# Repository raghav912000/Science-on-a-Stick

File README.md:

# Science-on-a-Stick
The thought of this project came when I was working in my physics lab. I made this project to overcome the limitations of performing experiments using conventional apparatus. Through this project, we can verify the value of acceleration due to gravity, Faraday's  Law and Lenz's Law with more accuracy and fewer efforts.  I use Arduino to convert analog value ( voltage across a coil) into digital values and send it to the laptop. I write a python code which receives data send by Arduino and plot the corresponding analog value. Through this curve, we can easily observe the maximum voltage across a coil. We can also verify Lenz's Law by the sinusoidal nature of the curve. I also use hall switch to give an interrupt to Arduino when a magnet passes it. By these interrupts, I can measure the time between any two points with more accuracy.
# trial

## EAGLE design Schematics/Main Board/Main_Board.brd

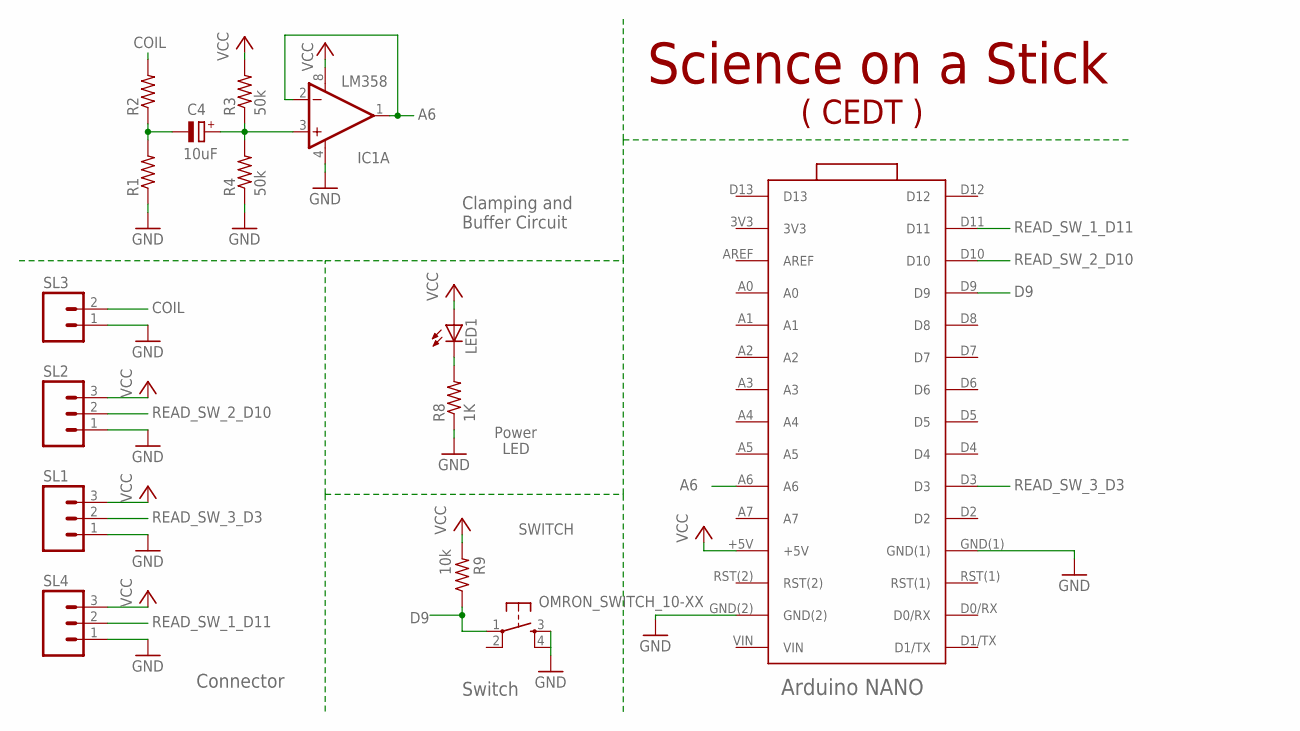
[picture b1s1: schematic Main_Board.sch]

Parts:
C4: 10uF; E2,5-5
IC1: LM358; DIP08
LED1: LED3MM
R1, R2: RESISTOR0207/7; 0207/7
R3, R4: 50k; 0207/7
R8: 1K; 0207/7
R9: 10k; 0207/7
SL1, SL2, SL4: M03; 03P
SL3: M02; 02P
SWITCH: OMRON_SWITCH_10-XX; B3F-10XX
U$1: ARDUINO_NANO_3_ARDUINO(NANO_3.0); ARDUINO_NANO_3_ARDUINO_NANO_30PIN

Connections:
A6: IC1.1 (OUT), IC1.2 (-IN), U$1.A6
CLAMP_SIGNAL: C4.+, IC1.3 (+IN), R3.1, R4.2
COIL: R2.2, SL3.2
D9: R9.1, SWITCH.1, U$1.D9
GND: IC1.4 (V-), R1.1, R4.1, R8.1, SL1.1, SL2.1, SL3.1, SL4.1, SWITCH.3 (S), SWITCH.4 (S1), U$1.GND(1), U$1.GND(2)
unnamed: C4.-, R1.2, R2.1
unnamed: LED1.K (C), R8.2
READ_SW_1_D11: SL4.2, U$1.D11
READ_SW_2_D10: SL2.2, U$1.D10
READ_SW_3_D3: SL1.2, U$1.D3
VCC: IC1.8 (V+), LED1.A, R3.2, R9.2, SL1.3, SL2.3, SL4.3, U$1.+5V

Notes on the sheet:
Arduino NANO
Science on a Stick
( CEDT )
Power
LED
Switch
Connector
Clamping and Buffer Circuit

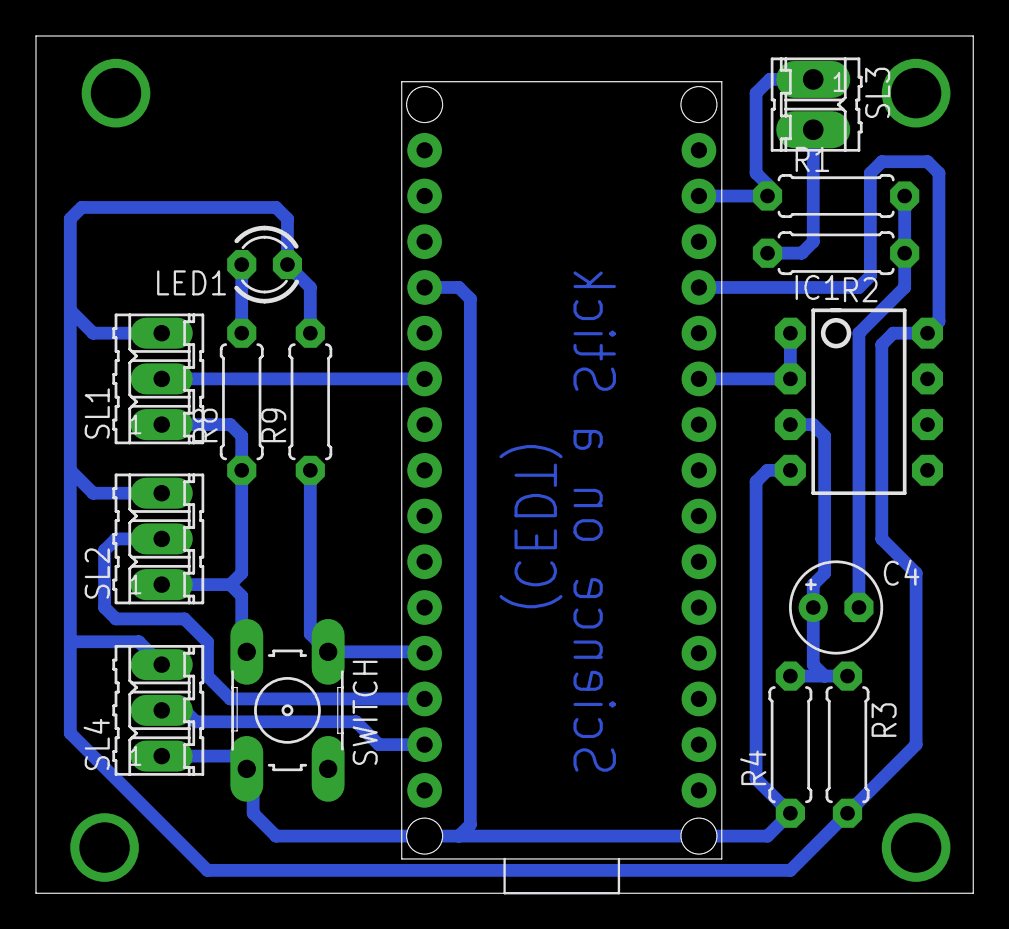
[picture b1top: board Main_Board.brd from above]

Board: 2 copper layers, 52.1 x 47.6 mm, 15 parts (0 on the bottom side), 11 nets.

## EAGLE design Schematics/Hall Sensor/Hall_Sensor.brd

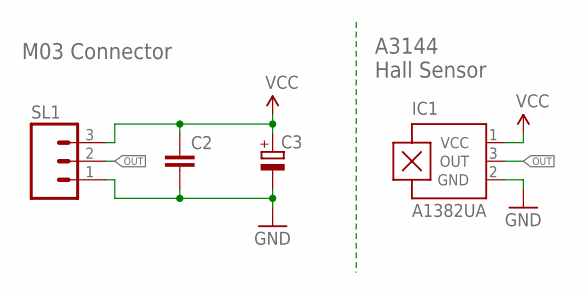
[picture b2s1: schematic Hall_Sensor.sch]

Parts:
C2: C-EU025-025X050; C025-025X050
C3: CPOL-EUE2,5-6E; E2,5-6E
IC1: A1382UA; SIP3-UA
SL1: M03; 03P

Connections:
GND: C2.2, C3.-, IC1.2 (GND), SL1.1
OUT: IC1.3 (OUT), SL1.2
VCC: C2.1, C3.+, IC1.1 (VCC), SL1.3

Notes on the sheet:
M03 Connector
A3144 Hall Sensor

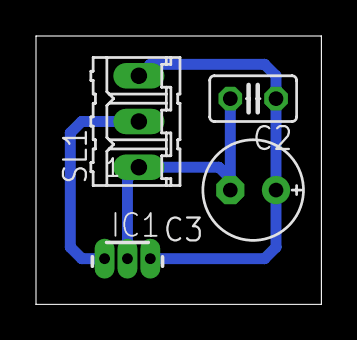
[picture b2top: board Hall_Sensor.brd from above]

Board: 2 copper layers, 15.9 x 14.9 mm, 4 parts (0 on the bottom side), 3 nets.

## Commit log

2018-10-21 Trial project

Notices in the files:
parts and their libraries:
SparkFun-AnalogIC: Licensing:Creative Commons ShareAlike 4.0 International - https://creativecommons.org/licenses/by-sa/4.0
